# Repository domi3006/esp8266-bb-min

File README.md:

# esp8266-bb-min

This repository contains only private projects with esp8266.

## WARNING

These designs are distributed in the hope that they will be useful, but WITHOUT ANY WARRANTY; even WITHOUT the implied warranty of MERCHANTABILITY or FITNESS FOR A PARTICULAR PURPOSE.

## esp8266-bb-min

This project is a minimal baseboard for an ESP-12F module.

## esp8266-shutter-ctrl

This project is a multi input/output expansion board for esp8266-bb-min.

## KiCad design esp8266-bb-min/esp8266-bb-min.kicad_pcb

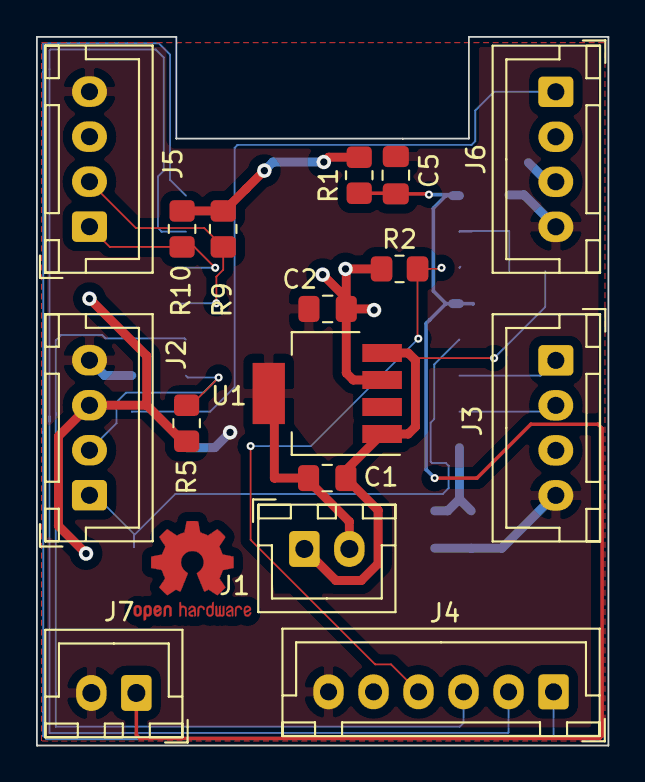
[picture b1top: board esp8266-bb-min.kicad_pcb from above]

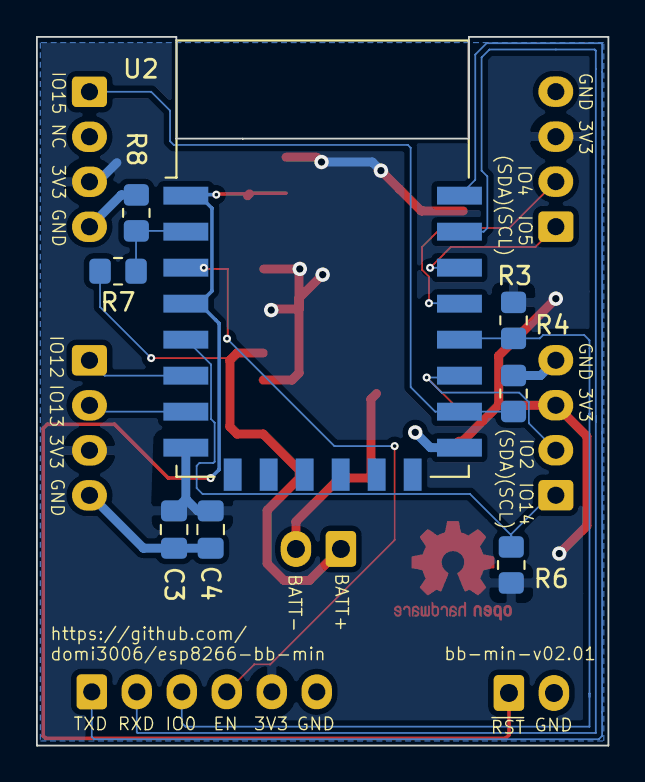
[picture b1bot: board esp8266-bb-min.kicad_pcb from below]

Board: 2 copper layers, 31.8 x 39.4 mm, 24 parts (8 on the bottom side), 16 nets.

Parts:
C1: 1uF; C_0805_2012Metric_Pad1.18x1.45mm_HandSolder
C2: 4.7uF; C_0805_2012Metric_Pad1.18x1.45mm_HandSolder
C3: 10uF; C_0805_2012Metric_Pad1.18x1.45mm_HandSolder
C4, C5: 100nF; C_0805_2012Metric_Pad1.18x1.45mm_HandSolder
J1, J7: Conn_01x02_Male; JST_XH_B2B-XH-A_1x02_P2.50mm_Vertical
J2, J3, J5, J6: Conn_01x04_Male; JST_XH_B4B-XH-A_1x04_P2.50mm_Vertical
J4: Conn_01x06_Male; JST_XH_B6B-XH-A_1x06_P2.50mm_Vertical
R1, R2, R3, R4: 10k; R_0805_2012Metric_Pad1.20x1.40mm_HandSolder
R5, R6, R9, R10: 4k7; R_0805_2012Metric_Pad1.20x1.40mm_HandSolder
R7: 47k; R_0805_2012Metric_Pad1.20x1.40mm_HandSolder
R8: 9k1; R_0805_2012Metric_Pad1.20x1.40mm_HandSolder
U1: LP38693MP-3.3; SOT-223-5
U2: ESP-12F; ESP-12E

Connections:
+3V3: C2.1, C3.2, C4.2, J2.3, J3.3, J4.5, J5.3, J6.3, R1.2, R2.1, R3.1, R5.2, R6.2, R9.2, R10.2, U1.3, U2.8
+BATT: C1.1, J1.1, R7.2, U1.1, U1.4
-BATT: C1.2, C2.2, C3.1, C4.1, C5.1, J1.2, J2.4, J3.4, J4.6, J5.4, J6.4, J7.2, R4.1, R8.1, U1.5, U2.15
/ESP_ADC: R7.1, R8.2, U2.2
/ESP_EN: J4.4, R2.2, U2.3
/ESP_GPIO0: J4.3, R3.2, U2.18
/ESP_GPIO2: J2.2, R5.1, U2.17
/ESP_GPIO4: J5.2, R9.1, U2.19
/ESP_GPIO5: J5.1, R10.1, U2.20
/ESP_GPIO12: J3.1, U2.6
/ESP_GPIO13: J3.2, U2.7
/ESP_GPIO14: J2.1, R6.1, U2.5
/ESP_GPIO15: J6.1, R4.2, U2.16
/ESP_RXD: J4.2, U2.21
/ESP_TXD: J4.1, U2.22
/~ESP_RST: C5.2, J7.1, R1.1, U2.1, U2.4

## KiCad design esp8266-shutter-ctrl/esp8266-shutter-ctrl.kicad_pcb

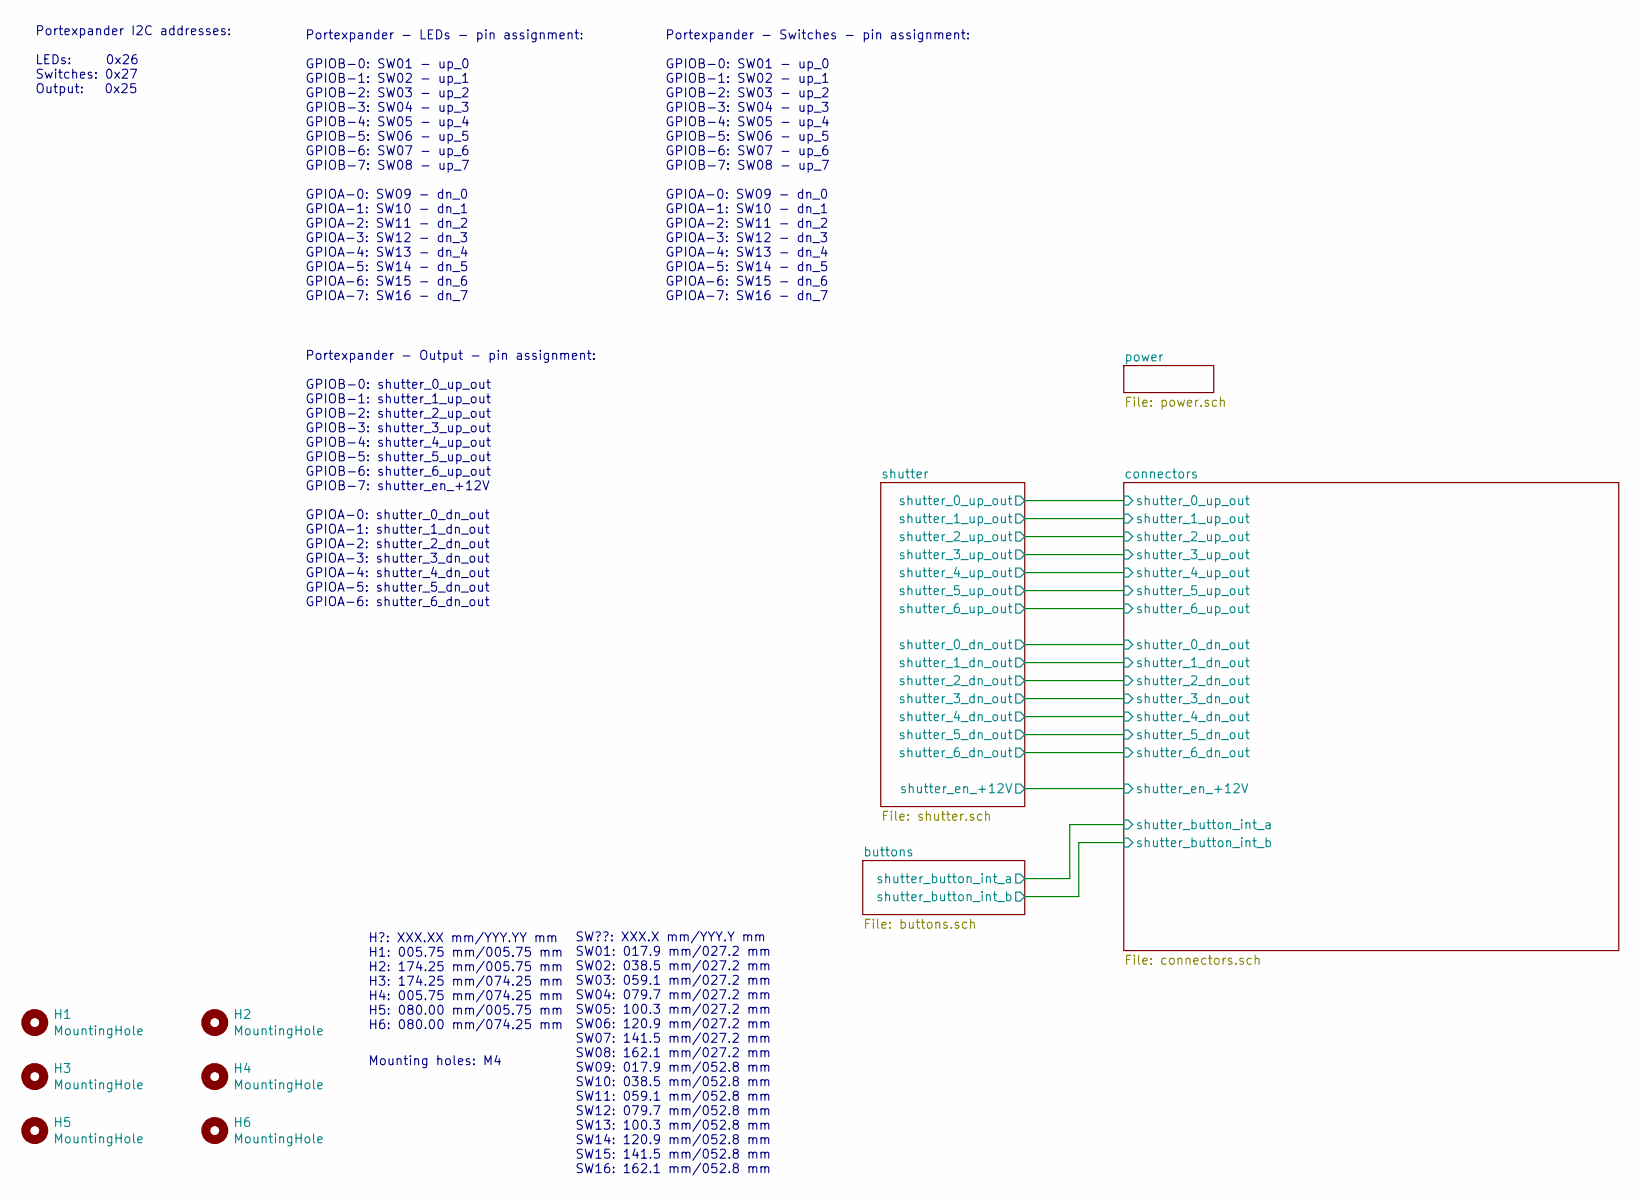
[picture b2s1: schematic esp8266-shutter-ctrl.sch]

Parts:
H1, H2, H3, H4, H5, H6: MountingHole; MountingHole_4.3mm_M4_ISO14580_Pad

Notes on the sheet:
H?: XXX.XX mm/YYY.YY mm H1: 005.75 mm/005.75 mm H2: 174.25 mm/005.75 mm H3: 174.25 mm/074.25 mm H4: 005.75 mm/074.25 mm H5: 080.00 mm/005.75 mm H6: 080.00 mm/074.25 mm
Portexpander I2C addresses: LEDs: 0x26 Switches: 0x27 Output: 0x25
SW??: XXX.X mm/YYY.Y mm SW01: 017.9 mm/027.2 mm SW02: 038.5 mm/027.2 mm SW03: 059.1 mm/027.2 mm SW04: 079.7 mm/027.2 mm SW05: 100.3 mm/027.2 mm SW06: 120.9 mm/027.2 mm SW07: 141.5 mm/027.2 mm SW08: 162.1 mm/027.2 mm SW09: 017.9 mm/052.8 mm SW10: 038.5 mm/052.8 mm SW11: 059.1 mm/052.8 mm SW12: 079.7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
Mounting holes: M4
Portexpander - Output - pin assignment: GPIOB-0: shutter_0_up_out GPIOB-1: shutter_1_up_out GPIOB-2: shutter_2_up_out GPIOB-3: shutter_3_up_out GPIOB-4: shutter_4_up_out GPIOB-5: shutter_5_up_out GPIOB-6: shutter_6_up_out GPIOB-7: shutter_en_+12V GPIOA-0: shutter_0_dn_out GPIOA-1: shutter_1_dn_out 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
Portexpander - Switches - pin assignment: GPIOB-0: SW01 - up_0 GPIOB-1: SW02 - up_1 GPIOB-2: SW03 - up_2 GPIOB-3: SW04 - up_3 GPIOB-4: SW05 - up_4 GPIOB-5: SW06 - up_5 GPIOB-6: SW07 - up_6 GPIOB-7: SW08 - up_7 GPIOA-0: SW09 - dn_0 GPIOA-1: SW10 - dn_1 GPIOA-2: SW11 - dn_2 GPIOA-3: SW12 - dn_3 GPIOA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
Portexpander - LEDs - pin assignment: GPIOB-0: SW01 - up_0 GPIOB-1: SW02 - up_1 GPIOB-2: SW03 - up_2 GPIOB-3: SW04 - up_3 GPIOB-4: SW05 - up_4 GPIOB-5: SW06 - up_5 GPIOB-6: SW07 - up_6 GPIOB-7: SW08 - up_7 GPIOA-0: SW09 - dn_0 GPIOA-1: SW10 - dn_1 GPIOA-2: SW11 - dn_2 GPIOA-3: SW12 - dn_3 GPIOA-4: 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

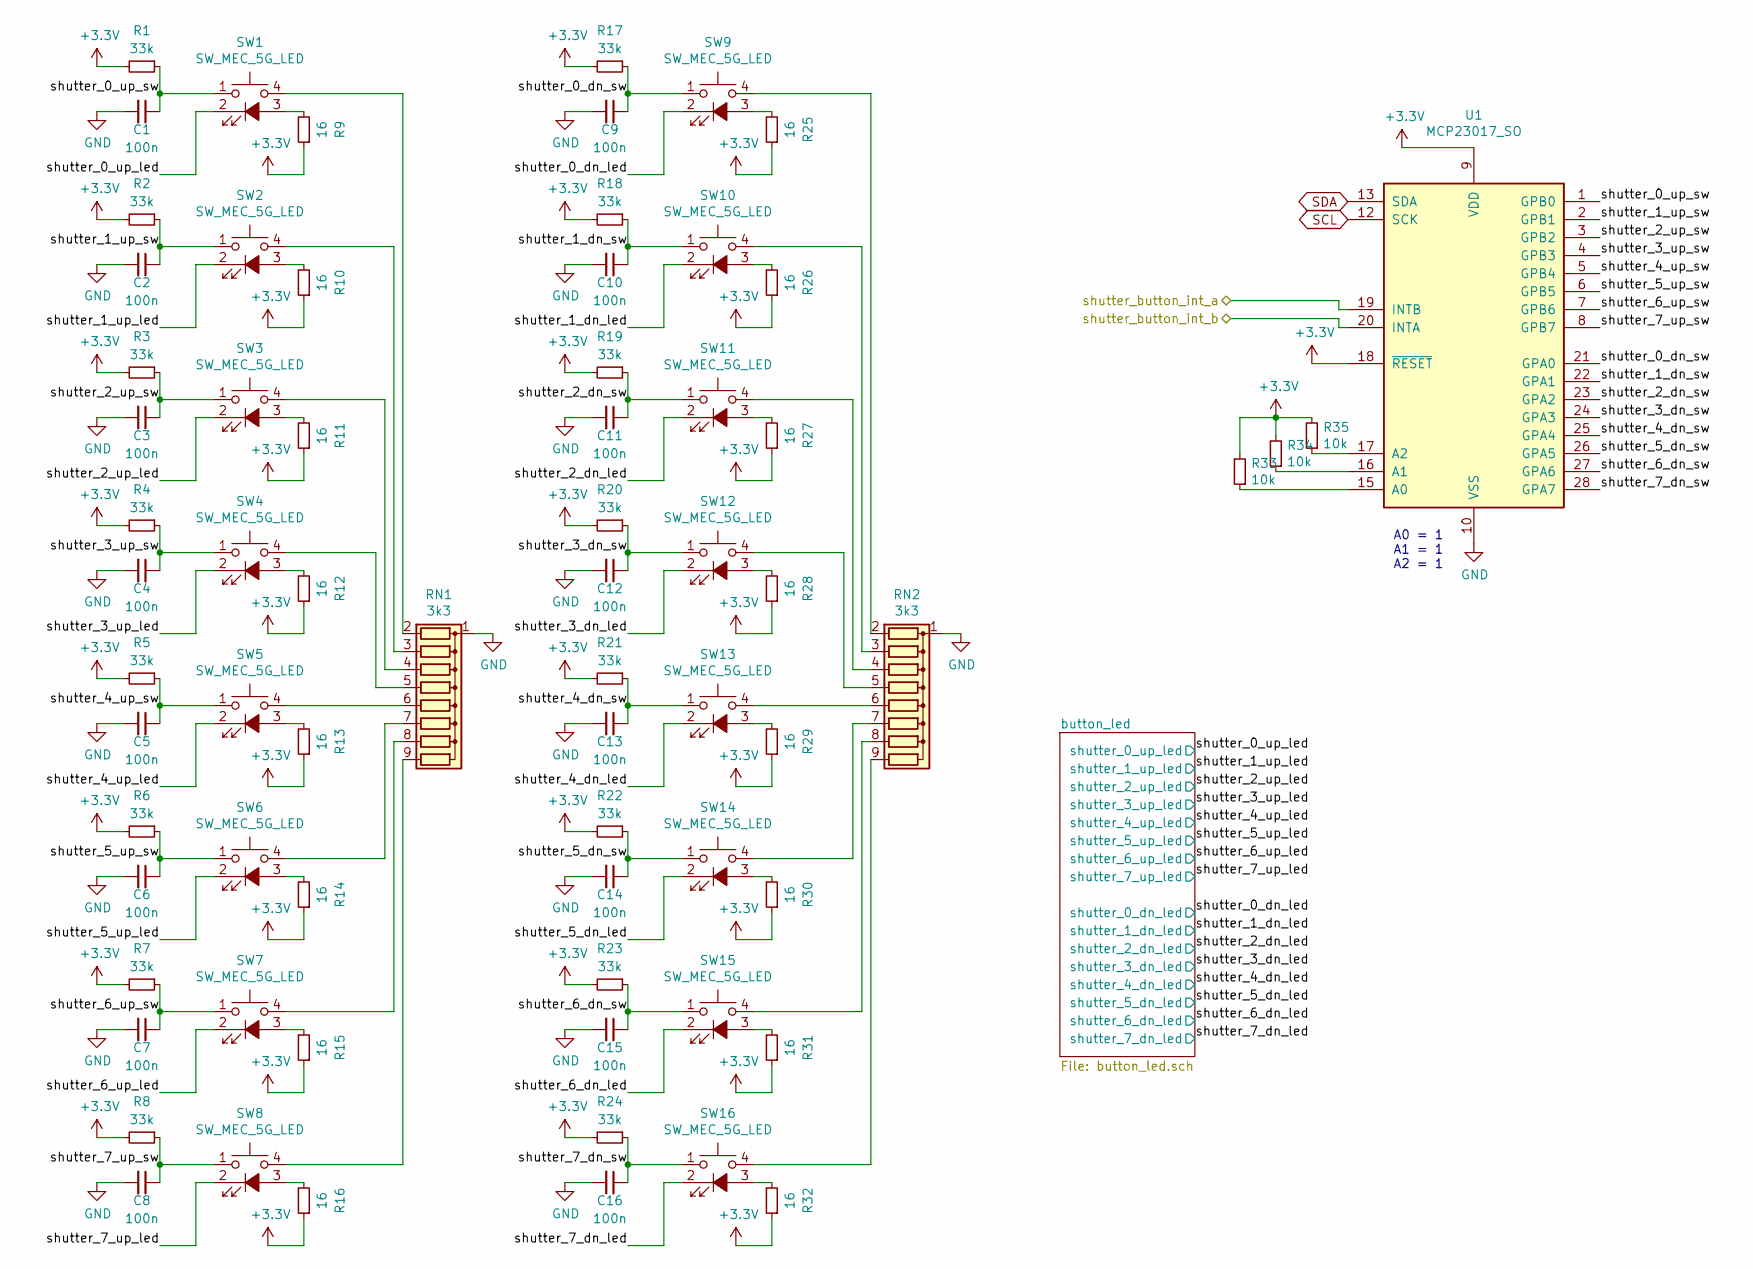
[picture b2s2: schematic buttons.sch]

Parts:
C1, C2, C3, C4, C5, C6, C7, C8, C9, C10, C11, C12, C13, C14, C15, C16: 100n; C_0805_2012Metric_Pad1.18x1.45mm_HandSolder
R1, R2, R3, R4, R5, R6, R7, R8, R17, R18, R19, R20, R21, R22, R23, R24: 33k; R_0805_2012Metric_Pad1.20x1.40mm_HandSolder
R9, R10, R11, R12, R13, R14, R15, R16, R25, R26, R27, R28, R29, R30, R31, R32: 16; R_0805_2012Metric_Pad1.20x1.40mm_HandSolder
R33, R34, R35: 10k; R_0805_2012Metric_Pad1.20x1.40mm_HandSolder
RN1, RN2: 3k3; R_Array_SIP9
SW1, SW2, SW3, SW4, SW5, SW6, SW7, SW8, SW9, SW10, SW11, SW12, SW13, SW14, SW15, SW16: SW_MEC_5G_LED; SW_MEC_5GSH9
U1: MCP23017_SO; SOIC-28W_7.5x17.9mm_P1.27mm

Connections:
+3V3: R1.2, R2.2, R3.2, R4.2, R5.2, R6.2, R7.2, R8.2, R9.1, R10.1, R11.1, R12.1, R13.1, R14.1, R15.1, R16.1, R17.2, R18.2, R19.2, R20.2, R21.2, R22.2, R23.2, R24.2, R25.1, R26.1, R27.1, R28.1, R29.1, R30.1, R31.1, R32.1, R33.2, R34.2, R35.2, U1.9 (VDD), U1.18 (~RESET~); also elsewhere on the board
/buttons/shutter_0_dn_led: SW9.2; also elsewhere on the board
/buttons/shutter_0_dn_sw: C9.1, R17.1, SW9.1, U1.21 (GPA0)
/buttons/shutter_0_up_led: SW1.2; also elsewhere on the board
/buttons/shutter_0_up_sw: C1.1, R1.1, SW1.1, U1.1 (GPB0)
/buttons/shutter_1_dn_led: SW10.2; also elsewhere on the board
/buttons/shutter_1_dn_sw: C10.1, R18.1, SW10.1, U1.22 (GPA1)
/buttons/shutter_1_up_led: SW2.2; also elsewhere on the board
/buttons/shutter_1_up_sw: C2.1, R2.1, SW2.1, U1.2 (GPB1)
/buttons/shutter_2_dn_led: SW11.2; also elsewhere on the board
/buttons/shutter_2_dn_sw: C11.1, R19.1, SW11.1, U1.23 (GPA2)
/buttons/shutter_2_up_led: SW3.2; also elsewhere on the board
/buttons/shutter_2_up_sw: C3.1, R3.1, SW3.1, U1.3 (GPB2)
/buttons/shutter_3_dn_led: SW12.2; also elsewhere on the board
/buttons/shutter_3_dn_sw: C12.1, R20.1, SW12.1, U1.24 (GPA3)
/buttons/shutter_3_up_led: SW4.2; also elsewhere on the board
/buttons/shutter_3_up_sw: C4.1, R4.1, SW4.1, U1.4 (GPB3)
/buttons/shutter_4_dn_led: SW13.2; also elsewhere on the board
/buttons/shutter_4_dn_sw: C13.1, R21.1, SW13.1, U1.25 (GPA4)
/buttons/shutter_4_up_led: SW5.2; also elsewhere on the board
/buttons/shutter_4_up_sw: C5.1, R5.1, SW5.1, U1.5 (GPB4)
/buttons/shutter_5_dn_led: SW14.2; also elsewhere on the board
/buttons/shutter_5_dn_sw: C14.1, R22.1, SW14.1, U1.26 (GPA5)
/buttons/shutter_5_up_led: SW6.2; also elsewhere on the board
/buttons/shutter_5_up_sw: C6.1, R6.1, SW6.1, U1.6 (GPB5)
/buttons/shutter_6_dn_led: SW15.2; also elsewhere on the board
/buttons/shutter_6_dn_sw: C15.1, R23.1, SW15.1, U1.27 (GPA6)
/buttons/shutter_6_up_led: SW7.2; also elsewhere on the board
/buttons/shutter_6_up_sw: C7.1, R7.1, SW7.1, U1.7 (GPB6)
/buttons/shutter_7_dn_led: SW16.2; also elsewhere on the board
/buttons/shutter_7_dn_sw: C16.1, R24.1, SW16.1, U1.28 (GPA7)
/buttons/shutter_7_up_led: SW8.2; also elsewhere on the board
/buttons/shutter_7_up_sw: C8.1, R8.1, SW8.1, U1.8 (GPB7)
/buttons/shutter_button_int_a: U1.19 (INTB); also elsewhere on the board
/buttons/shutter_button_int_b: U1.20 (INTA); also elsewhere on the board
GND: C1.2, C2.2, C3.2, C4.2, C5.2, C6.2, C7.2, C8.2, C9.2, C10.2, C11.2, C12.2, C13.2, C14.2, C15.2, C16.2, RN1.1 (common), RN2.1 (common), U1.10 (VSS); also elsewhere on the board
unnamed: R9.2, SW1.3 (K)
unnamed: R10.2, SW2.3 (K)
unnamed: R11.2, SW3.3 (K)
unnamed: R12.2, SW4.3 (K)
unnamed: R13.2, SW5.3 (K)
unnamed: R14.2, SW6.3 (K)
unnamed: R15.2, SW7.3 (K)
unnamed: R16.2, SW8.3 (K)
unnamed: R25.2, SW9.3 (K)
unnamed: R26.2, SW10.3 (K)
unnamed: R27.2, SW11.3 (K)
unnamed: R28.2, SW12.3 (K)
unnamed: R29.2, SW13.3 (K)
unnamed: R30.2, SW14.3 (K)
unnamed: R31.2, SW15.3 (K)
unnamed: R32.2, SW16.3 (K)
unnamed: R33.1, U1.15 (A0)
unnamed: R34.1, U1.16 (A1)
unnamed: R35.1, U1.17 (A2)
unnamed: RN1.2 (R1), SW1.4 (A)
unnamed: RN1.3 (R2), SW2.4 (A)
unnamed: RN1.4 (R3), SW3.4 (A)
unnamed: RN1.5 (R4), SW4.4 (A)
unnamed: RN1.6 (R5), SW5.4 (A)
unnamed: RN1.7 (R6), SW6.4 (A)
unnamed: RN1.8 (R7), SW7.4 (A)
unnamed: RN1.9 (R8), SW8.4 (A)
unnamed: RN2.2 (R1), SW9.4 (A)
unnamed: RN2.3 (R2), SW10.4 (A)
unnamed: RN2.4 (R3), SW11.4 (A)
unnamed: RN2.5 (R4), SW12.4 (A)
unnamed: RN2.6 (R5), SW13.4 (A)
unnamed: RN2.7 (R6), SW14.4 (A)
unnamed: RN2.8 (R7), SW15.4 (A)
unnamed: RN2.9 (R8), SW16.4 (A)
SCL: U1.12 (SCK); also elsewhere on the board
SDA: U1.13 (SDA); also elsewhere on the board

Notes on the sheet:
A0 = 1 A1 = 1 A2 = 1

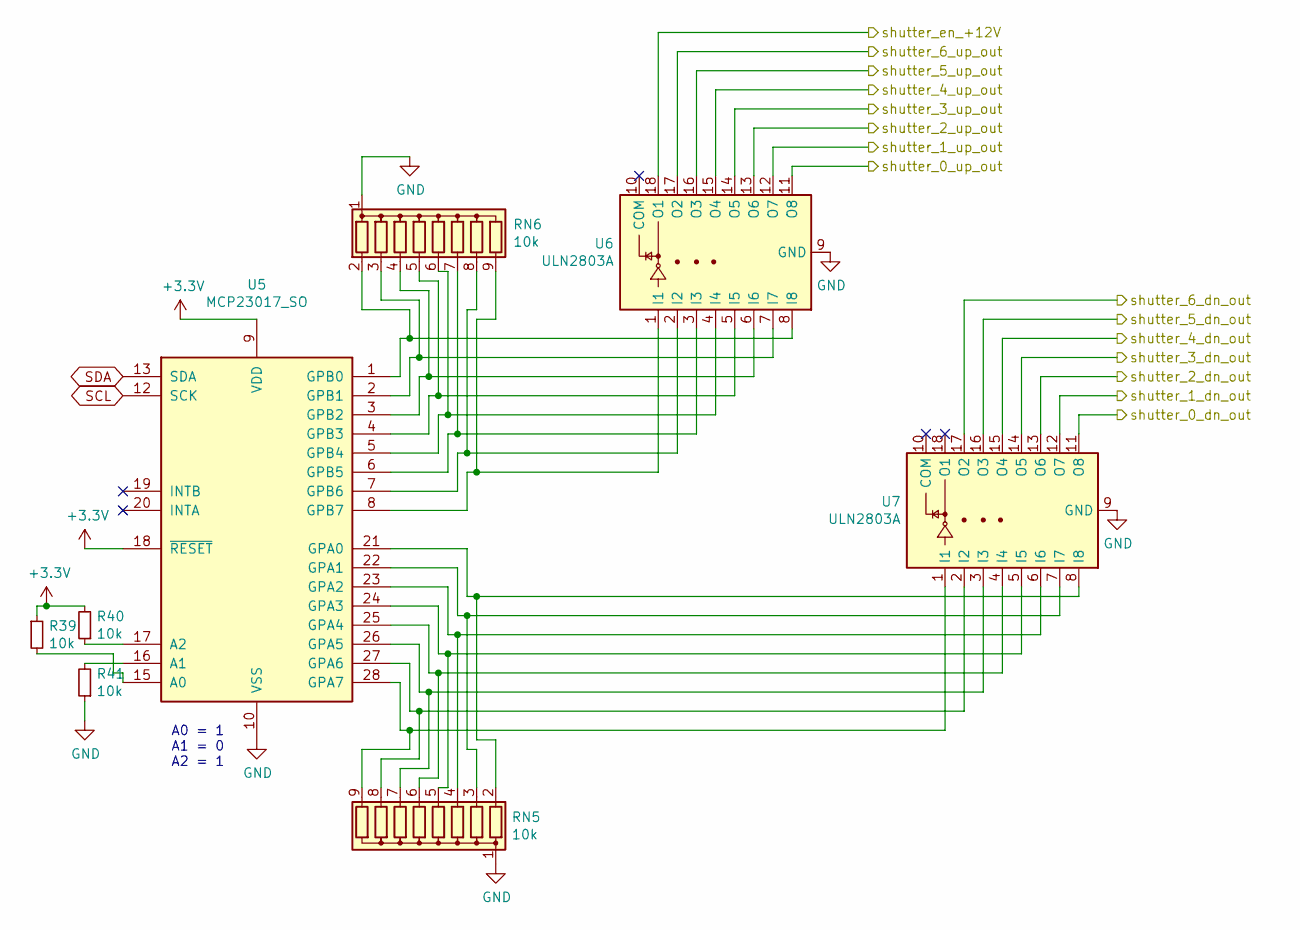
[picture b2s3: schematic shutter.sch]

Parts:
R39, R40, R41: 10k; R_0805_2012Metric_Pad1.20x1.40mm_HandSolder
RN5, RN6: 10k; R_Array_SIP9
U5: MCP23017_SO; SOIC-28W_7.5x17.9mm_P1.27mm
U6, U7: ULN2803A; SOIC-18W_7.5x11.6mm_P1.27mm

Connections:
+3V3: R39.1, R40.2, U5.9 (VDD), U5.18 (~RESET~); also elsewhere on the board
/connectors/shutter_0_dn_out: U7.11 (O8); also elsewhere on the board
/connectors/shutter_0_up_out: U6.11 (O8); also elsewhere on the board
/connectors/shutter_1_dn_out: U7.12 (O7); also elsewhere on the board
/connectors/shutter_1_up_out: U6.12 (O7); also elsewhere on the board
/connectors/shutter_2_dn_out: U7.13 (O6); also elsewhere on the board
/connectors/shutter_2_up_out: U6.13 (O6); also elsewhere on the board
/connectors/shutter_3_dn_out: U7.14 (O5); also elsewhere on the board
/connectors/shutter_3_up_out: U6.14 (O5); also elsewhere on the board
/connectors/shutter_4_dn_out: U7.15 (O4); also elsewhere on the board
/connectors/shutter_4_up_out: U6.15 (O4); also elsewhere on the board
/connectors/shutter_5_dn_out: U7.16 (O3); also elsewhere on the board
/connectors/shutter_5_up_out: U6.16 (O3); also elsewhere on the board
/connectors/shutter_6_dn_out: U7.17 (O2); also elsewhere on the board
/connectors/shutter_6_up_out: U6.17 (O2); also elsewhere on the board
/connectors/shutter_en_+12V: U6.18 (O1); also elsewhere on the board
GND: R41.1, RN5.1 (common), RN6.1 (common), U5.10 (VSS), U6.9 (GND), U7.9 (GND); also elsewhere on the board
unnamed: R39.2, U5.15 (A0)
unnamed: R40.1, U5.17 (A2)
unnamed: R41.2, U5.16 (A1)
unnamed: RN5.2 (R1), U5.21 (GPA0), U7.8 (I8)
unnamed: RN5.3 (R2), U5.22 (GPA1), U7.7 (I7)
unnamed: RN5.4 (R3), U5.23 (GPA2), U7.6 (I6)
unnamed: RN5.5 (R4), U5.24 (GPA3), U7.5 (I5)
unnamed: RN5.6 (R5), U5.25 (GPA4), U7.4 (I4)
unnamed: RN5.7 (R6), U5.26 (GPA5), U7.3 (I3)
unnamed: RN5.8 (R7), U5.27 (GPA6), U7.2 (I2)
unnamed: RN5.9 (R8), U5.28 (GPA7), U7.1 (I1)
unnamed: RN6.2 (R1), U5.1 (GPB0), U6.8 (I8)
unnamed: RN6.3 (R2), U5.2 (GPB1), U6.7 (I7)
unnamed: RN6.4 (R3), U5.3 (GPB2), U6.6 (I6)
unnamed: RN6.5 (R4), U5.4 (GPB3), U6.5 (I5)
unnamed: RN6.6 (R5), U5.5 (GPB4), U6.4 (I4)
unnamed: RN6.7 (R6), U5.6 (GPB5), U6.3 (I3)
unnamed: RN6.8 (R7), U5.7 (GPB6), U6.2 (I2)
unnamed: RN6.9 (R8), U5.8 (GPB7), U6.1 (I1)
SCL: U5.12 (SCK); also elsewhere on the board
SDA: U5.13 (SDA); also elsewhere on the board

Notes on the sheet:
A0 = 1 A1 = 0 A2 = 1

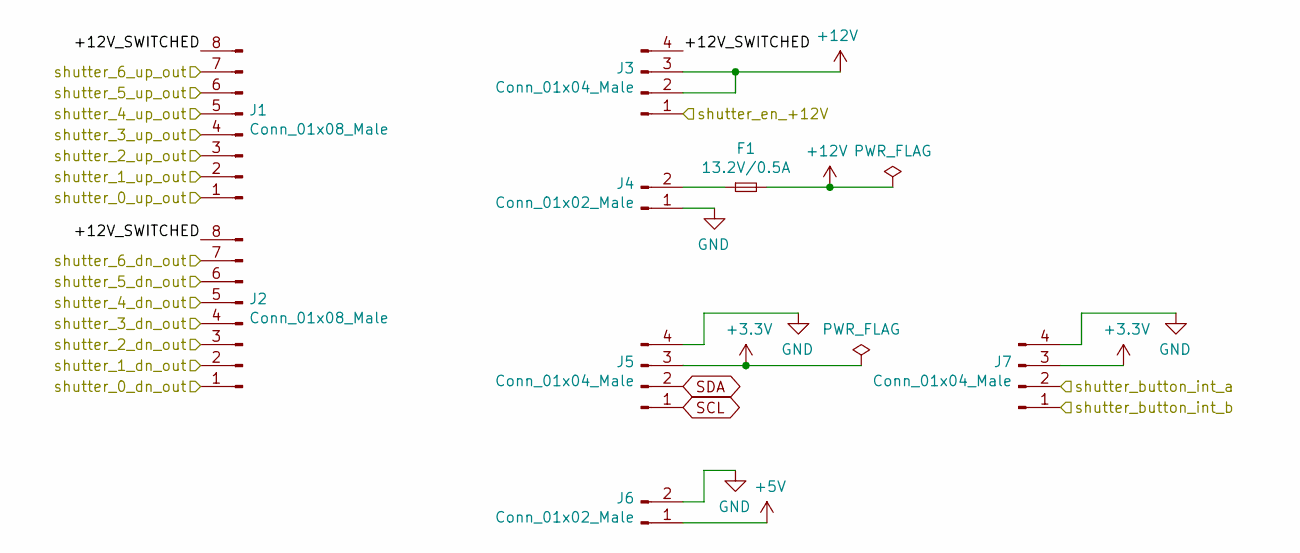
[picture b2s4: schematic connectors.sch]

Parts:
F1: 13.2V/0.5A; R_1206_3216Metric_Pad1.30x1.75mm_HandSolder
J1, J2: Conn_01x08_Male; Wago_734-138_1x08_P3.50mm_Vertical
J3: Conn_01x04_Male; Wago_734-134_1x04_P3.50mm_Vertical
J4: Conn_01x02_Male; Wago_734-132_1x02_P3.50mm_Vertical
J5, J7: Conn_01x04_Male; JST_XH_B4B-XH-A_1x04_P2.50mm_Vertical
J6: Conn_01x02_Male; JST_XH_B2B-XH-A_1x02_P2.50mm_Vertical

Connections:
+3V3: J5.3, J7.3; also elsewhere on the board
+5V: J6.1; also elsewhere on the board
+12V: F1.2, J3.2, J3.3; also elsewhere on the board
/buttons/shutter_button_int_a: J7.2; also elsewhere on the board
/buttons/shutter_button_int_b: J7.1; also elsewhere on the board
/connectors/+12V_SWITCHED: J1.8, J2.8, J3.4
/connectors/shutter_0_dn_out: J2.1; also elsewhere on the board
/connectors/shutter_0_up_out: J1.1; also elsewhere on the board
/connectors/shutter_1_dn_out: J2.2; also elsewhere on the board
/connectors/shutter_1_up_out: J1.2; also elsewhere on the board
/connectors/shutter_2_dn_out: J2.3; also elsewhere on the board
/connectors/shutter_2_up_out: J1.3; also elsewhere on the board
/connectors/shutter_3_dn_out: J2.4; also elsewhere on the board
/connectors/shutter_3_up_out: J1.4; also elsewhere on the board
/connectors/shutter_4_dn_out: J2.5; also elsewhere on the board
/connectors/shutter_4_up_out: J1.5; also elsewhere on the board
/connectors/shutter_5_dn_out: J2.6; also elsewhere on the board
/connectors/shutter_5_up_out: J1.6; also elsewhere on the board
/connectors/shutter_6_dn_out: J2.7; also elsewhere on the board
/connectors/shutter_6_up_out: J1.7; also elsewhere on the board
/connectors/shutter_en_+12V: J3.1; also elsewhere on the board
GND: J4.1, J5.4, J6.2, J7.4; also elsewhere on the board
unnamed: F1.1, J4.2
SCL: J5.1; also elsewhere on the board
SDA: J5.2; also elsewhere on the board

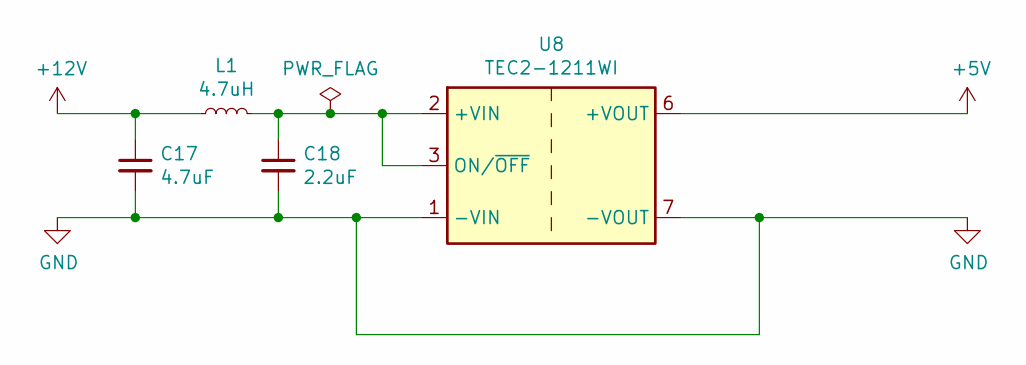
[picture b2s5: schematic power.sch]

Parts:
C17: 4.7uF; C_0805_2012Metric_Pad1.18x1.45mm_HandSolder
C18: 2.2uF; C_0805_2012Metric_Pad1.18x1.45mm_HandSolder
L1: 4.7uH; L_Radial_D8.7mm_P5.00mm_Fastron_07HCP
U8: TEC2-1211WI; Converter_DCDC_TRACO_TMR-xxxx_THT

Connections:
+5V: U8.6 (+VOUT); also elsewhere on the board
+12V: C17.1, L1.1; also elsewhere on the board
GND: C17.2, C18.2, U8.1 (-VIN), U8.7 (-VOUT); also elsewhere on the board
unnamed: C18.1, L1.2, U8.2 (+VIN), U8.3 (ON/~OFF)

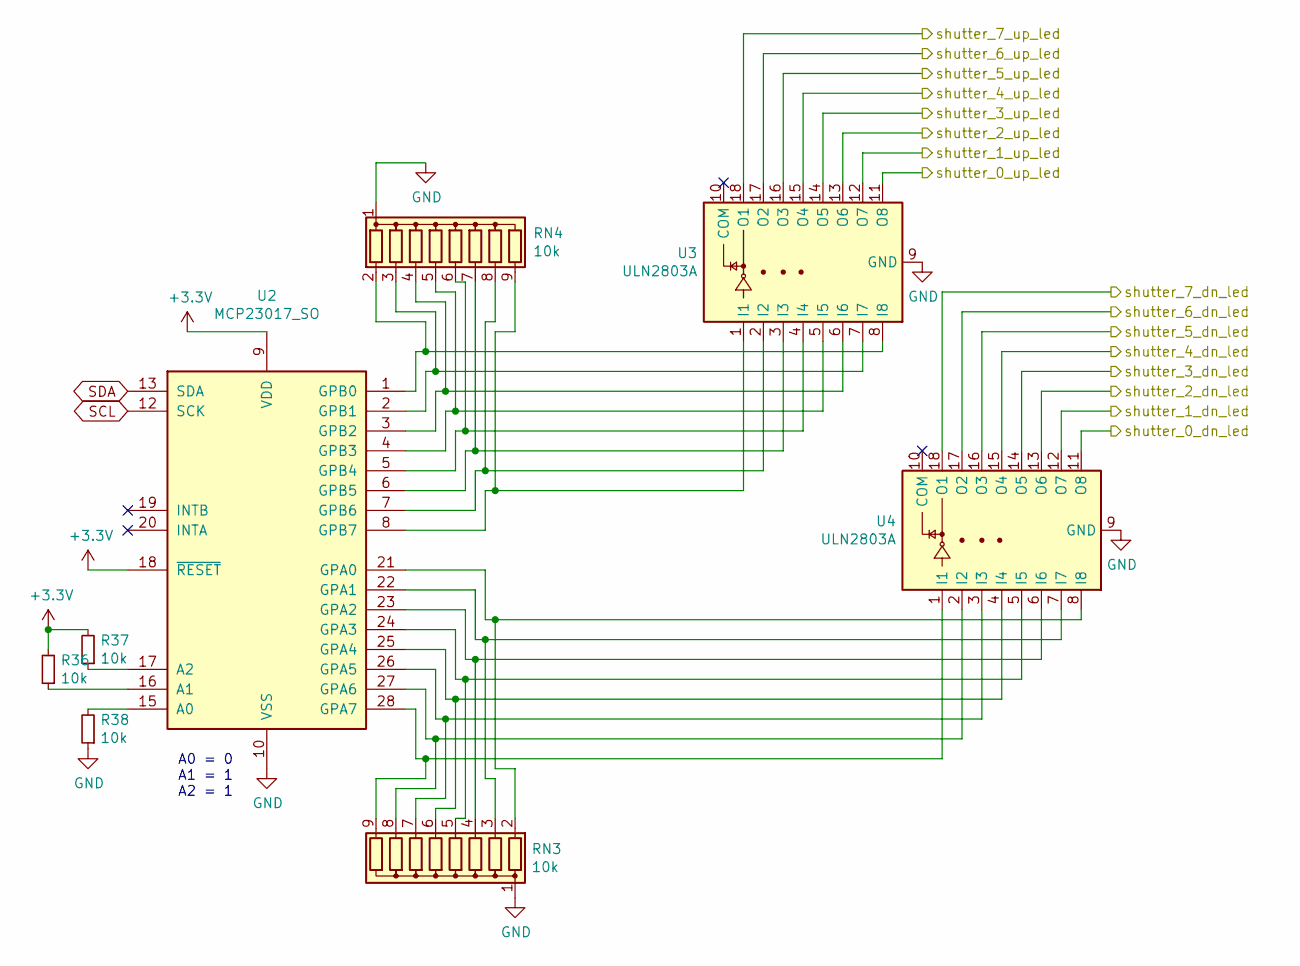
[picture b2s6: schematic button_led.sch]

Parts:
R36, R37, R38: 10k; R_0805_2012Metric_Pad1.20x1.40mm_HandSolder
RN3, RN4: 10k; R_Array_SIP9
U2: MCP23017_SO; SOIC-28W_7.5x17.9mm_P1.27mm
U3, U4: ULN2803A; SOIC-18W_7.5x11.6mm_P1.27mm

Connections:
+3V3: R36.2, R37.2, U2.9 (VDD), U2.18 (~RESET~); also elsewhere on the board
/buttons/shutter_0_dn_led: U4.11 (O8); also elsewhere on the board
/buttons/shutter_0_up_led: U3.11 (O8); also elsewhere on the board
/buttons/shutter_1_dn_led: U4.12 (O7); also elsewhere on the board
/buttons/shutter_1_up_led: U3.12 (O7); also elsewhere on the board
/buttons/shutter_2_dn_led: U4.13 (O6); also elsewhere on the board
/buttons/shutter_2_up_led: U3.13 (O6); also elsewhere on the board
/buttons/shutter_3_dn_led: U4.14 (O5); also elsewhere on the board
/buttons/shutter_3_up_led: U3.14 (O5); also elsewhere on the board
/buttons/shutter_4_dn_led: U4.15 (O4); also elsewhere on the board
/buttons/shutter_4_up_led: U3.15 (O4); also elsewhere on the board
/buttons/shutter_5_dn_led: U4.16 (O3); also elsewhere on the board
/buttons/shutter_5_up_led: U3.16 (O3); also elsewhere on the board
/buttons/shutter_6_dn_led: U4.17 (O2); also elsewhere on the board
/buttons/shutter_6_up_led: U3.17 (O2); also elsewhere on the board
/buttons/shutter_7_dn_led: U4.18 (O1); also elsewhere on the board
/buttons/shutter_7_up_led: U3.18 (O1); also elsewhere on the board
GND: R38.1, RN3.1 (common), RN4.1 (common), U2.10 (VSS), U3.9 (GND), U4.9 (GND); also elsewhere on the board
unnamed: R36.1, U2.16 (A1)
unnamed: R37.1, U2.17 (A2)
unnamed: R38.2, U2.15 (A0)
unnamed: RN3.2 (R1), U2.21 (GPA0), U4.8 (I8)
unnamed: RN3.3 (R2), U2.22 (GPA1), U4.7 (I7)
unnamed: RN3.4 (R3), U2.23 (GPA2), U4.6 (I6)
unnamed: RN3.5 (R4), U2.24 (GPA3), U4.5 (I5)
unnamed: RN3.6 (R5), U2.25 (GPA4), U4.4 (I4)
unnamed: RN3.7 (R6), U2.26 (GPA5), U4.3 (I3)
unnamed: RN3.8 (R7), U2.27 (GPA6), U4.2 (I2)
unnamed: RN3.9 (R8), U2.28 (GPA7), U4.1 (I1)
unnamed: RN4.2 (R1), U2.1 (GPB0), U3.8 (I8)
unnamed: RN4.3 (R2), U2.2 (GPB1), U3.7 (I7)
unnamed: RN4.4 (R3), U2.3 (GPB2), U3.6 (I6)
unnamed: RN4.5 (R4), U2.4 (GPB3), U3.5 (I5)
unnamed: RN4.6 (R5), U2.5 (GPB4), U3.4 (I4)
unnamed: RN4.7 (R6), U2.6 (GPB5), U3.3 (I3)
unnamed: RN4.8 (R7), U2.7 (GPB6), U3.2 (I2)
unnamed: RN4.9 (R8), U2.8 (GPB7), U3.1 (I1)
SCL: U2.12 (SCK); also elsewhere on the board
SDA: U2.13 (SDA); also elsewhere on the board

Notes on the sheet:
A0 = 0 A1 = 1 A2 = 1

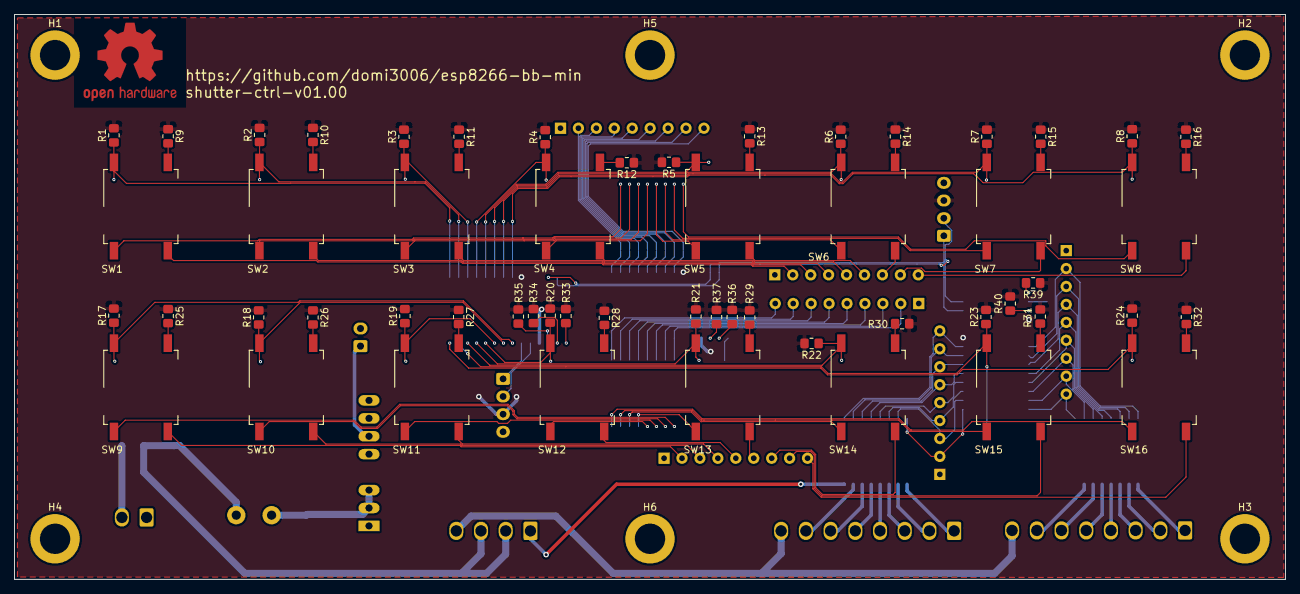
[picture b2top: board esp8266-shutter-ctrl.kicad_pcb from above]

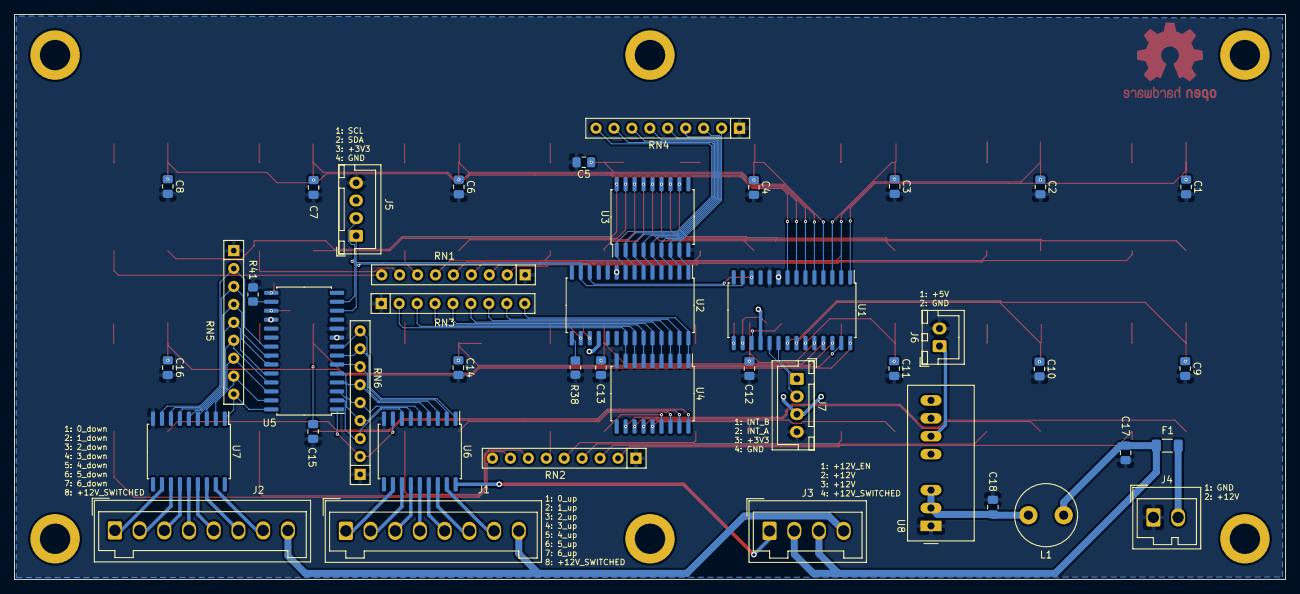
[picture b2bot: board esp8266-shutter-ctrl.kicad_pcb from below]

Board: 2 copper layers, 180.0 x 80.0 mm, 104 parts (43 on the bottom side), 131 nets.

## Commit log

2020-11-05 added digikey kicad library
2020-11-05 added aisler project library
2020-11-05 added own libraries
2020-11-05 sch: initial commit
2020-11-05 added empty pcb and imported aisler config
2020-11-05 sch: fixed value of C2
2020-11-05 pcb: imported footprints
2020-11-05 pcb: intial commit
2020-11-05 *: added title and revision
2020-11-05 introduced CI
    inspired by:
    https://github.com/INTI-CMNB/kicad_ci_test
2020-11-05 ci: added sample kiplot
2020-11-05 *: cleanup of erc errors
2020-11-05 CI: simplify
2020-11-05 CI: Makefile:
    gerbers, excellon_drill, gerber_drills, position
2020-11-05 readme: initial commit
2020-11-05 FIXME: CI: disable pcb_print
    Error of piplot:
    kiplot -d Fabrication -s all print_front print_bottom
    Using config file: esp8266-bb-min.kiplot.yaml
    Using SCH file: esp8266-bb-min.sch
    - 'Print Front + F.SilkS' (print_front) [pdf_pcb_print]
    ERROR:In output `'Print Front + F.SilkS' (print_front) [pdf_pcb_print]`: Inner layer `Front (0 'No description' Front)` is not valid for this board (kibot.kibot.kiplot - kiplot.py:264)
2020-11-05 pcb: updated text
2020-11-20 ci: updated and simplified
2020-12-02 readme: updated badge
2020-12-02 kiplot.yml: taken from junkdna/esp8266-bb-mini
    origin:
    https://github.com/junkdna/esp8266-bb-mini/blob/be65a8c972490a57bcfe9a4fff546e4e88d32184/esp8266-bb-mini.kiplot.yaml
2020-12-02 gitignore: added Fabrication folder
2020-12-02 makefile: updated due to new kiplot.yml
2020-12-02 ci: updated due to makefile change
2020-12-02 makefile: moved and made more flexible
2020-12-02 gitignore: excluded files beginning with .
2020-12-04 ci: used github internal container registry
2020-12-04 gitignore: .github excluded
2020-12-05 sch: addressed issue domi3006/esp8266-bb-min#3
2020-12-05 sch: addressed issue domi3006/esp8266-bb-min#5
2020-12-05 sch: addressed issue domi3006/esp8266-bb-min#4
2020-12-05 sch: added adc sensing for battery
2020-12-05 sch: used ceramic condensator X5R for C2
2020-12-05 pcb: redesign of pcb
2020-12-05 pcb: corrected position of J5 label
2020-12-05 pcb: corrected resistor values for ADC
2020-12-05 pcb: removed dangling track part
2020-12-05 sch: added pullups for I2C
2020-12-05 pcb: corrected SCL/SDA pinout
2020-12-05 sch: corrected resistor values for ADC
2020-12-05 pcb: corrected placement of ohw symbol
2020-12-05 pro: reduced clearing
2020-12-05 sch: updated version string
2020-12-05 sch: corrected SCL/SDA pinout
2020-12-05 pcb: corrected label positions
2020-12-05 pcb: updated version string
2020-12-05 pcb: added pullups for I2C
2020-12-05 pcb: updated copper planes
2020-12-05 shutter-ctrl: initial commit
2020-12-06 shutter-ctrl: sch: first try
2020-12-06 shutter-ctrl: pcb: first try
2020-12-06 shutter-ctrl: sch: added fuse and updated description
2020-12-06 ci: increased dpi of png export
2020-12-06 shutter-ctrl: added fuse and increased track width for +12V
2020-12-06 ci: moved kiplot config to root
2020-12-06 makefile: added error propagation and introduced ROOT variable
2020-12-06 shutter-ctrl: pcb: added description
2020-12-06 shutter-ctrl: pcb: improved 3V3 plane connection to J7
2020-12-06 readme: updated
2020-12-06 shutter-ctrl: sch: updated comments and titles
2020-12-06 shutter-ctrl: pcb: updated due to changes in schematic
2020-12-06 ci: esp8266-bb-min: merged tests and artifacts to gen_artifacts
2020-12-06 ci: create-release: initial commit
2020-12-06 ci: esp8266-bb-min: renamed to build.yml
2020-12-06 ci: build: reworded steps
2020-12-06 ci: create-release: reworded steps
2020-12-06 ci: create-release: split in artifact generation and upload
2020-12-06 ci: create-release: removed master branch from action
2020-12-06 ci: create-release: fixed download and zip
2020-12-06 ci: create-release: reworded checkout step
2020-12-06 ci: build: reworded checkout step
2020-12-06 ci: create-release: switched to svenstaro/upload-release-action
2020-12-06 makefile: copy kicad_pcb files to corresponding output directory
2020-12-06 ci: create-release: fixed error "no such file or directory, stat '~/fabrication.zip'"
2020-12-06 ci: create-release: trigger at all kind of tags
2020-12-06 ci: create-release: corrected asset filename
2020-12-16 bb-min: pcb: updated silkscreen
2020-12-16 bb-min: sch: updated version
2020-12-16 bb-min: pcb: updated version
